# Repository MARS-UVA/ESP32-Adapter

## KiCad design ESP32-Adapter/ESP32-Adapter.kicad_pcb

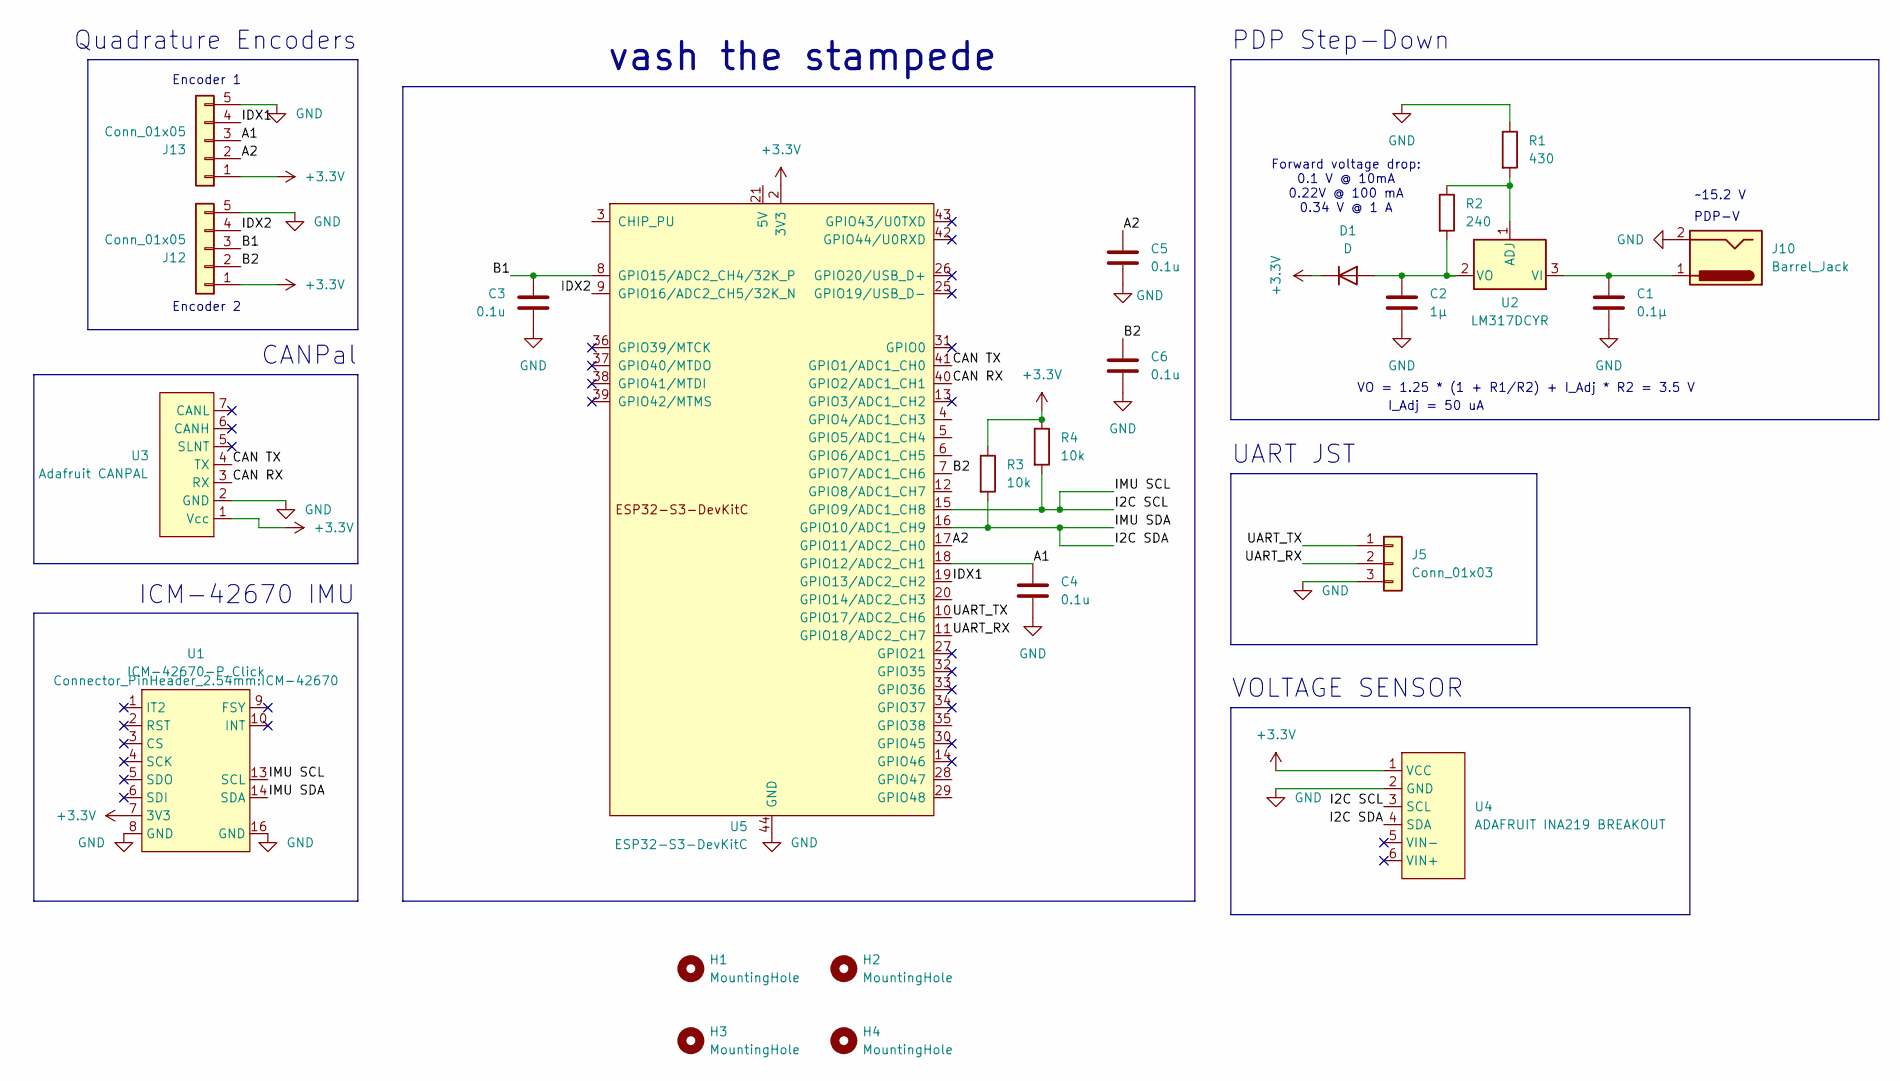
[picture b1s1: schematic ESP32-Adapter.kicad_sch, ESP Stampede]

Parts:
C1: 0.1µ; C_0402_1005Metric
C2: 1µ; C_0402_1005Metric
C3, C4, C5, C6: 0.1u; C_0402_1005Metric
D1: D; USC_TOS
H1, H2, H3, H4: MountingHole; MountingHole_4.5mm
J5: Conn_01x03; JST_XH_B3B-XH-A_1x03_P2.50mm_Vertical
J10: Barrel_Jack; BarrelJack_CUI_PJ-063AH_Horizontal
J12, J13: Conn_01x05; JST_XH_B5B-XH-A_1x05_P2.50mm_Vertical
R1: 430; R_0402_1005Metric
R2: 240; R_0402_1005Metric
R3, R4: 10k; R_0402_1005Metric
U1: ICM-42670-P_Click; ICM-42670
U2: LM317DCYR; SOT-223-3_TabPin2
U3: Adafruit CANPAL; canpal
U4: ADAFRUIT INA219 BREAKOUT; INA219 Breakout
U5: ESP32-S3-DevKitC

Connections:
+3.3V: D1.1 (K), J12.1, J13.1, R3.1, R4.1, U1.7 (3V3), U3.1 (Vcc), U4.1 (VCC), U5.1 (3V3), U5.2 (3V3)
/A1: C4.1, J13.3, U5.18 (GPIO12/ADC2_CH1)
/A2: C5.1, J13.2, U5.17 (GPIO11/ADC2_CH0)
/B1: C3.1, J12.3, U5.8 (GPIO15/ADC2_CH4/32K_P)
/B2: C6.1, J12.2, U5.7 (GPIO7/ADC1_CH6)
/CAN RX: U3.3 (RX), U5.40 (GPIO2/ADC1_CH1)
/CAN TX: U3.4 (TX), U5.41 (GPIO1/ADC1_CH0)
/I2C SCL: R4.2, U1.13 (SCL), U4.3 (SCL), U5.15 (GPIO9/ADC1_CH8)
/I2C SDA: R3.2, U1.14 (SDA), U4.4 (SDA), U5.16 (GPIO10/ADC1_CH9)
/IDX1: J13.4, U5.19 (GPIO13/ADC2_CH2)
/IDX2: J12.4, U5.9 (GPIO16/ADC2_CH5/32K_N)
/UART_RX: J5.2, U5.11 (GPIO18/ADC2_CH7)
/UART_TX: J5.1, U5.10 (GPIO17/ADC2_CH6)
GND: C1.2, C2.2, C3.2, C4.2, C5.2, C6.2, J5.3, J10.2, J12.5, J13.5, R1.1, U1.8 (GND), U1.16 (GND), U3.2 (GND), U4.2 (GND), U5.22 (GND), U5.23 (GND), U5.24 (GND), U5.44 (GND)
unnamed: C2.1, D1.2 (A), R2.2, U2.2 (VO)
unnamed: R1.2, R2.1, U2.1 (ADJ)
unnamed: C1.1, J10.1, U2.3 (VI)

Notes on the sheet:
VOLTAGE SENSOR
ICM-42670 IMU
Encoder 2
PDP-V
~15.2 V
vash the stampede
Forward voltage drop: 0.1 V @ 10mA 0.22V @ 100 mA 0.34 V @ 1 A
Encoder 1
Quadrature Encoders
I_Adj = 50 uA
PDP Step-Down
UART JST
VO = 1.25 * (1 + R1/R2) + I_Adj * R2 = 3.5 V
CANPal

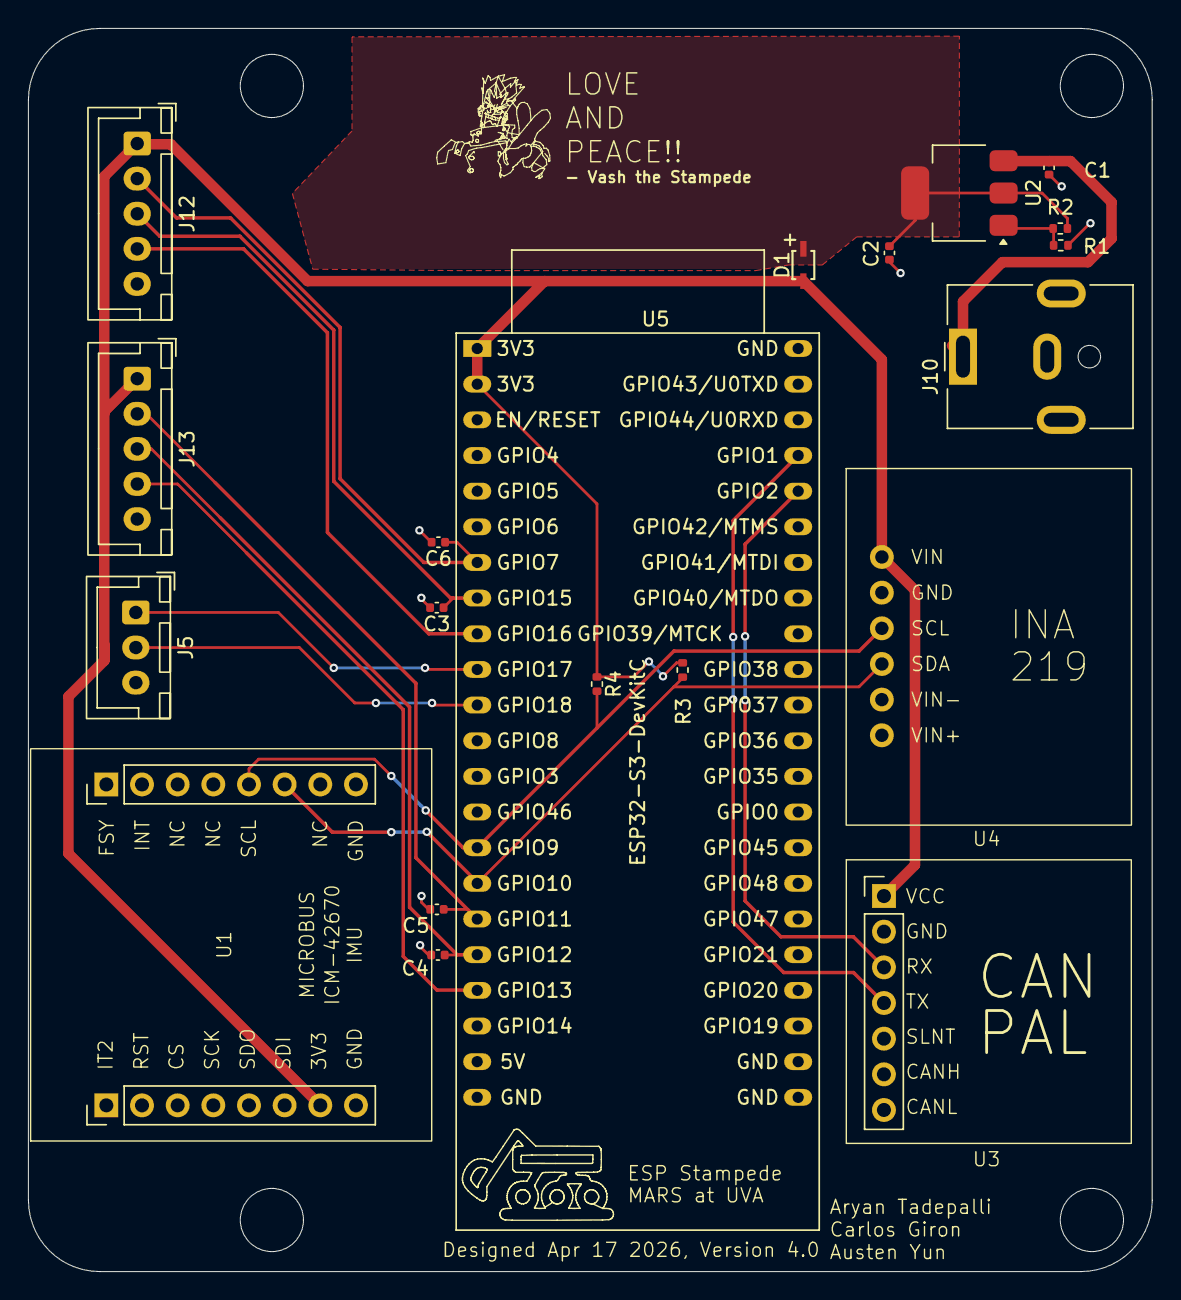
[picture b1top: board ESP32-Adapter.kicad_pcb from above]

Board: 2 copper layers, 80.1 x 88.5 mm, 24 parts (0 on the bottom side), 17 nets.

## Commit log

2026-01-30 Create blank project
    Add global symbols and footprints. Set board constraints.
2026-02-01 complete adapter board schem
2026-02-03 create pcb
2026-02-03 finish general routing of board
2026-02-03 add board outline and mounting holes
2026-02-03 add mars logo and vash the stampede art
2026-02-03 fix small layout error
2026-02-03 turn canpal to not face screw
2026-02-03 finish first version of neopixel board
2026-02-10 final to this branch
2026-02-18 Redo board partially
2026-02-18 new board
2026-02-18 finish board
2026-02-19 Update Schematic
    Added annotations. Modified value of R1 in voltage-stepdown circuit. Added footprint for diode and changed footprint for LM317
2026-02-19 Add GND Plane
    Added GND Plane. Sized down PCB. Added some 3D models.
2026-02-19 fix some precarious traces
2026-02-19 fix some text alignment
2026-02-19 a bit of trace fixing
2026-02-19 hole size inconsistencies, fixed
2026-02-19 final fixes for the day sorry
2026-02-19 clean up some strange traces
2026-02-19 final
2026-02-19 Update CANPal footprint pin spacing
2026-02-19 Add port labels
2026-02-19 Refresh the fill
2026-02-19 post clearance DRC check
    DRC check brought up clearance improvements, quick fix
2026-02-20 generate gerbers
2026-03-19 retracing for proper gpio layout
2026-03-19 fix schematic, symbols, footprints
2026-03-31 updates updates
2026-03-31 austne yun pins adjusted
2026-03-31 connect v sensor pins:
2026-03-31 close kicad tsk
2026-04-02 esp32s3 pcb finish prelim
2026-04-03 Add i2c pullup resistors
2026-04-03 Add holes
    Moved connectors on left side of board to place holes in the same location as ESP32C5 Adapter Board
2026-04-03 Bring logo to top copper
2026-04-03 Update Gerbers
2026-04-10 Replace S3 Dev kit w C5
2026-04-12 add bypass caps
2026-04-12 close kicad sob
2026-04-12 add caps to A2 and B2
2026-04-17 added uart connections
    Used gpio 17 & 18 for tx and rx
2026-04-20 made j5 vertical as per jarad e
2026-04-22 generate new gerbers
2026-04-23 Generate new gerbers (again)
2026-04-23 Change JST-XH connectors to vertical
